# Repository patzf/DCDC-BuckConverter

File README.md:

# DCDC-BuckConverter
HWE Projekt 25/26

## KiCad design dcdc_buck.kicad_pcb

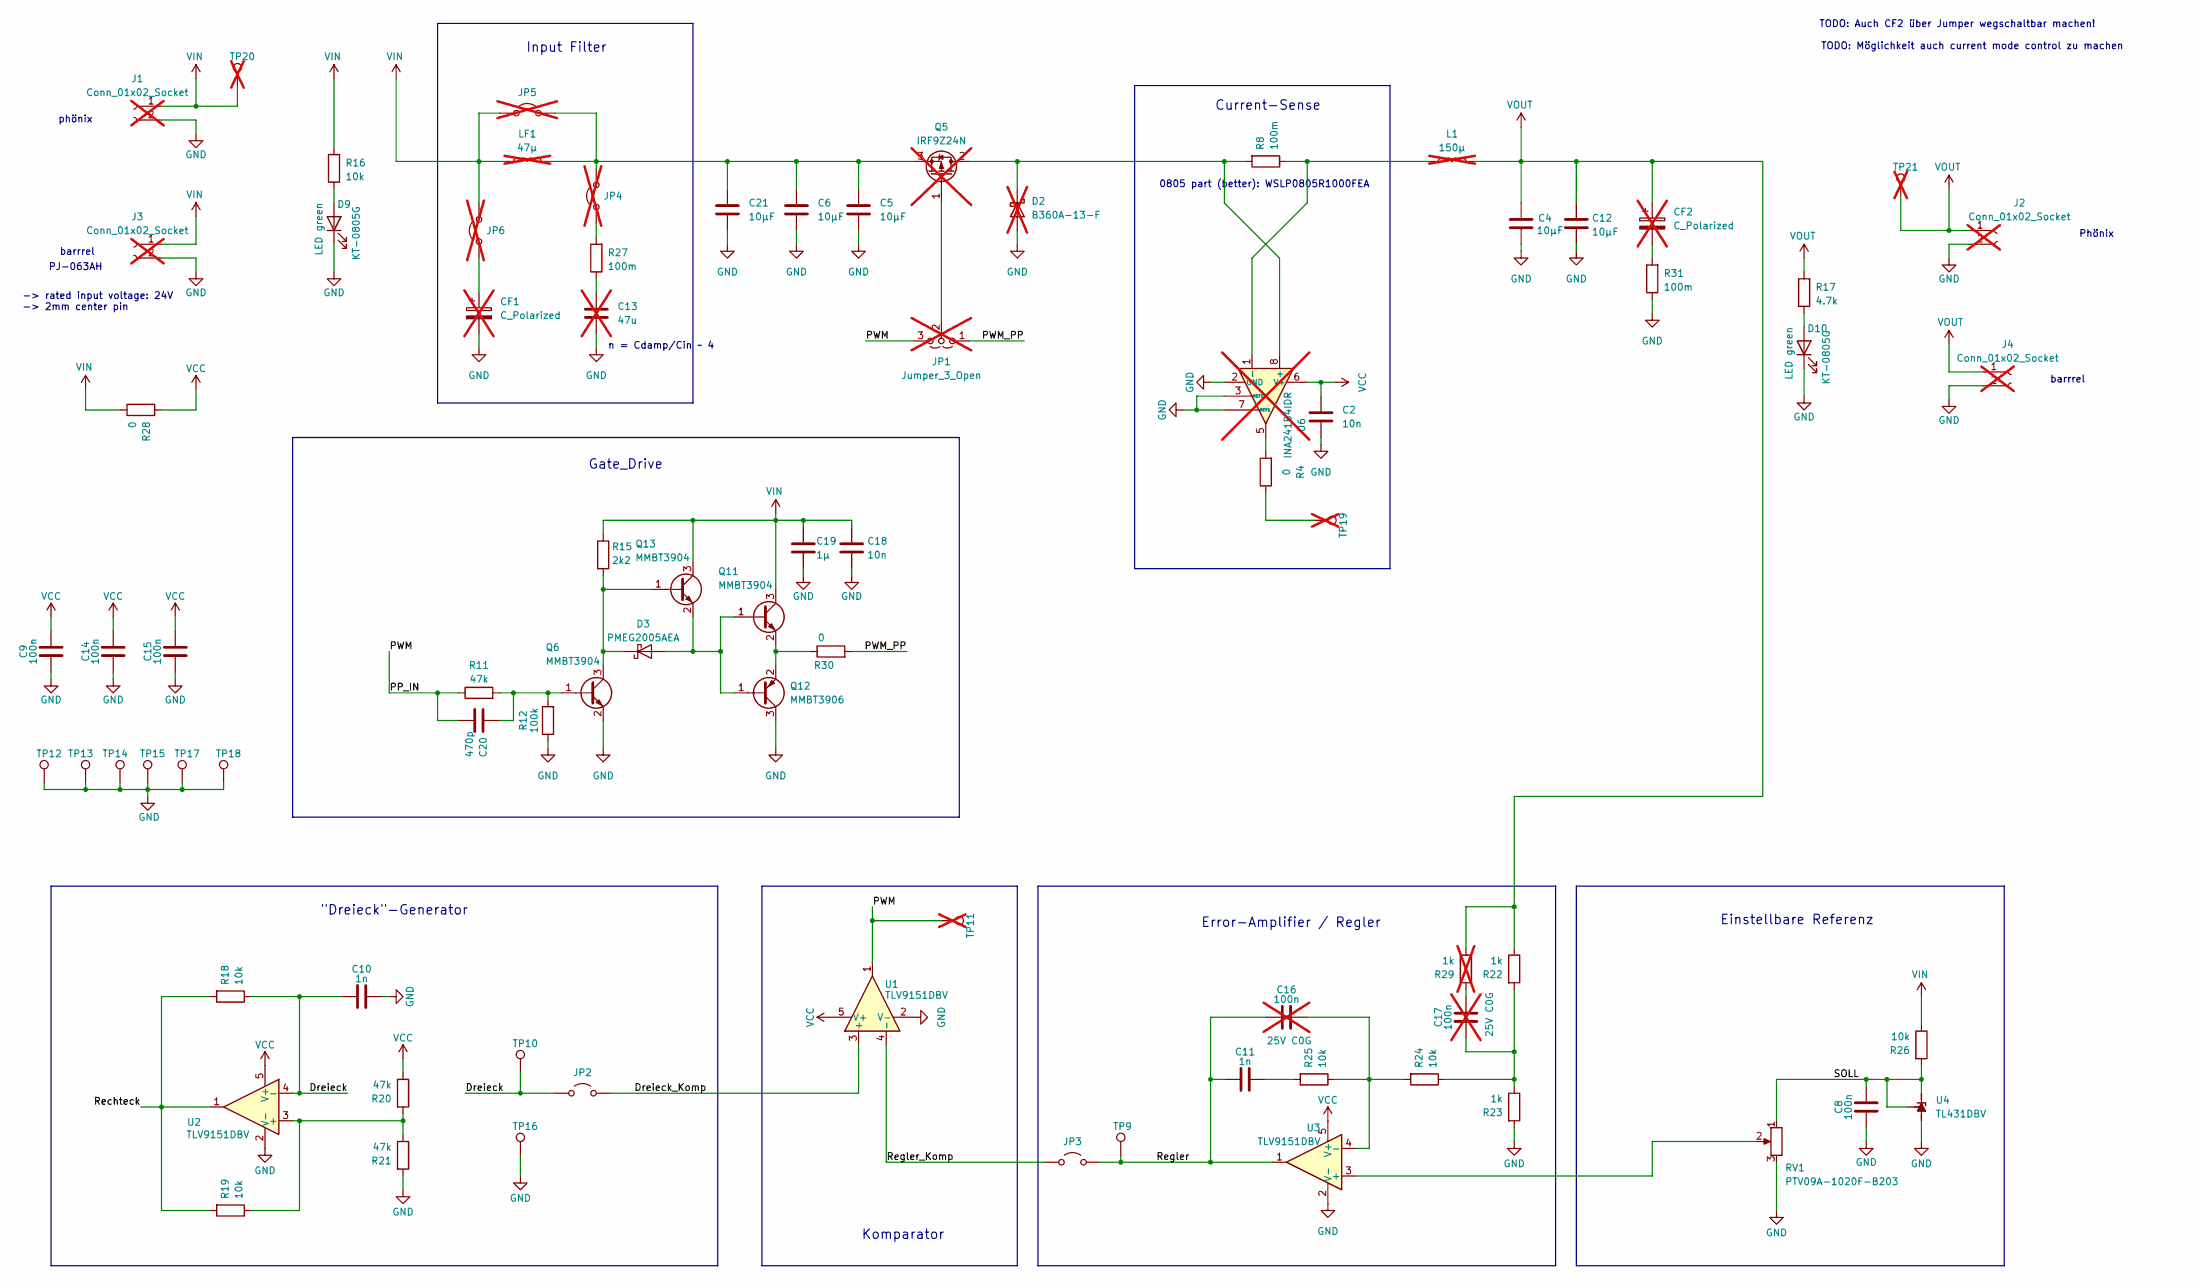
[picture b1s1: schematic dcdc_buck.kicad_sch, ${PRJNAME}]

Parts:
C2, C18: 10n; C_0603_1608Metric_Pad1.08x0.95mm_HandSolder; LCSC Part # C57112
C4, C5, C6, C12, C21: 10µF; C_1206_3216Metric; LCSC Part # C13585
C8: 100n; C_0805_2012Metric; LCSC Part # C49678
C9, C14, C15: 100n; C_0402_1005Metric; LCSC Part # C307331
C10, C11: 1n; C_0805_2012Metric; LCSC Part # C46653
C13: 47u; C_1206_3216Metric; not fitted
C16, C17: 100n; C_0805_2012Metric; not fitted
C19: 1µ; C_0805_2012Metric_Pad1.18x1.45mm_HandSolder; LCSC Part # C28323
C20: 470p; C_0603_1608Metric_Pad1.08x0.95mm_HandSolder; LCSC Part # C1620
CF1, CF2: C_Polarized; CP_Elec_6.3x7.7; not fitted
D2: B360A-13-F; D_SMC; LCSC Part # C94193; not fitted
D3: PMEG2005AEA; D_SOD-323; LCSC Part # C179428
D9, D10: KT-0805G; LED_0805_2012Metric; LCSC Part # C2297
J1, J2: Conn_01x02_Socket; PhoenixContact_MC_1,5_2-G-3.81_1x02_P3.81mm_Horizontal; not fitted
J3, J4: Conn_01x02_Socket; BarrelJack_CUI_PJ-063AH_Horizontal; not fitted
JP1: Jumper_3_Open; PinHeader_1x03_P2.54mm_Vertical; not fitted
JP2, JP3: Jumper_2_Open; PinHeader_1x02_P2.54mm_Vertical; LCSC Part # C492401
JP4, JP5, JP6: Jumper_2_Open; PinHeader_1x02_P2.54mm_Vertical; LCSC Part # C492401; not fitted
L1: 150µ; L_Wurth_WE-PD2-1054; LCSC Part # C6404682; not fitted
LF1: 47µ; L_Wurth_WE-PD2-1054; not fitted
Q5: IRF9Z24N; TO-220-3_Vertical; LCSC Part # C2576; not fitted
Q6, Q11, Q13: MMBT3904; SOT-23; LCSC Part # C20526
Q12: MMBT3906; SOT-23; LCSC Part # C7420354
R4: 0; R_0603_1608Metric_Pad0.98x0.95mm_HandSolder; LCSC Part # C21189
R8, R27, R31: 100m; R_1206_3216Metric_Pad1.30x1.75mm_HandSolder; LCSC Part # C25334
R11: 47k; R_0603_1608Metric_Pad0.98x0.95mm_HandSolder; LCSC Part # C25819
R12: 100k; R_0603_1608Metric_Pad0.98x0.95mm_HandSolder; LCSC Part # C25803
R15: 2k2; R_0805_2012Metric_Pad1.20x1.40mm_HandSolder; LCSC Part # C17520
R16, R18, R19, R24, R25, R26: 10k; R_0805_2012Metric; LCSC Part # C17414
R17: 4.7k; R_0805_2012Metric; LCSC Part # C17673
R20, R21: 47k; R_0805_2012Metric; LCSC Part # C17713
R22, R23: 1k; R_0805_2012Metric; LCSC Part # C17513
R28, R30: 0; R_1206_3216Metric_Pad1.30x1.75mm_HandSolder; LCSC Part # C17888
R29: 1k; R_0805_2012Metric; LCSC Part # C17513; not fitted
RV1: PTV09A-1020F-B203; Potentiometer_Bourns_PTV09A-1_Single_Vertical
TP9, TP10: TestPoint; TP_Keystone_5010-5014_Multipurpose; LCSC Part # C2906765
TP11, TP19, TP20, TP21: TestPoint; TP_Keystone_5010-5014_Multipurpose; LCSC Part # C2906765; not fitted
TP12, TP13, TP14, TP15, TP16, TP17, TP18: TestPoint_Keystone_5019; TestPoint_Keystone_5019_Miniature; LCSC Part # C238131
U1, U2, U3: TLV9151DBV; SOT-23-5; LCSC Part # C1517408
U4: TL431DBV; SOT-23-5
U6: INA241B4IDR; SOIC-8_3.9x4.9mm_P1.27mm; LCSC Part # C21260962; not fitted

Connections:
/Dreieck: C10.2, JP2.1 (A), R18.1, TP10.1 (1_1), U2.4 (-)
/Dreieck_Komp: JP2.2 (B), U1.3 (+)
/PP_IN: C20.2, JP1.3 (B), R11.1, TP11.1 (1_1), U1.1
/PWM_PP: JP1.1 (A), R30.2
/Rechteck: R18.2, R19.2, U2.1
/Regler: C11.2, C16.2, JP3.1 (A), TP9.1 (1_1), U3.1
/Regler_Komp: JP3.2 (B), U1.4 (-)
/SOLL: C8.1, R26.2, RV1.1, U4.3 (K), U4.4 (REF)
GND: C2.2, C4.2, C5.2, C6.2, C8.2, C9.1, C10.1, C12.2, C13.2, C14.1, C15.1, C18.2, C19.2, C21.2, CF1.2, D2.2 (A), D9.1 (K), D10.1 (K), J1.2, J2.2, J3.2, J4.2, Q6.2 (E), Q12.3 (C), R12.1, R21.2, R23.2, R31.1, RV1.3, TP12.1 (1_1), TP13.1 (1_1), TP14.1 (1_1), TP15.1 (1_1), TP16.1 (1_1), TP17.1 (1_1), TP18.1 (1_1), U1.2 (V-), U2.2 (V-), U3.2 (V-), U4.5 (A), U6.2 (GND), U6.3 (REF2), U6.4 (GND), U6.7 (REF1)
unnamed: C11.1, R25.2
unnamed: C13.1, R27.1
unnamed: C17.1, R29.2
unnamed: C17.2, R22.2, R23.1, R24.1
unnamed: CF2.2, R31.2
unnamed: D2.1 (K), Q5.2 (D), R8.2, U6.8 (+)
unnamed: D3.2 (A), Q11.1 (B), Q12.1 (B), Q13.2 (E)
unnamed: D3.1 (K), Q6.3 (C), Q13.1 (B), R15.2
unnamed: D9.2 (A), R16.1
unnamed: D10.2 (A), R17.1
unnamed: JP1.2 (C), Q5.1 (G)
unnamed: C5.1, C6.1, C21.1, JP4.1 (A), JP5.1 (A), LF1.2, Q5.3 (S)
unnamed: JP4.2 (B), R27.2
unnamed: CF1.1, JP6.2 (B)
unnamed: C20.1, Q6.1 (B), R11.2, R12.2
unnamed: Q11.2 (E), Q12.2 (E), R30.1
unnamed: R4.1, TP19.1 (1_1)
unnamed: R4.2, U6.5
unnamed: R19.1, R20.2, R21.1, U2.3 (+)
unnamed: RV1.2, U3.3 (+)
unnamed: C16.1, R24.2, R25.1, U3.4 (-)
unnamed: L1.1, R8.1, U6.1 (-)
VCC: C2.1, C9.2, C14.2, C15.2, R20.1, R28.2, U1.5 (V+), U2.5 (V+), U3.5 (V+), U6.6 (V+)
VIN: C18.1, C19.1, J1.1, J3.1, JP5.2 (B), JP6.1 (A), LF1.1, Q11.3 (C), Q13.3 (C), R15.1, R16.2, R26.1, R28.1, TP20.1 (1_1)
VOUT: C4.1, C12.1, CF2.1, J2.1, J4.1, L1.2, R17.2, R22.1, R29.1, TP21.1 (1_1)

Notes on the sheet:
TODO: Möglichkeit auch current mode control zu machen
-> rated input voltage: 24V -> 2mm center pin
Current-Sense
Komparator
barrrel
"Dreieck"-Generator
Phönix
Einstellbare Referenz
Gate_Drive
n = Cdamp/Cin ~ 4
TODO: Auch CF2 über Jumper wegschaltbar machen!
Error-Amplifier / Regler
0805 part (better): WSLP0805R1000FEA
PJ-063AH
Input Filter
phönix

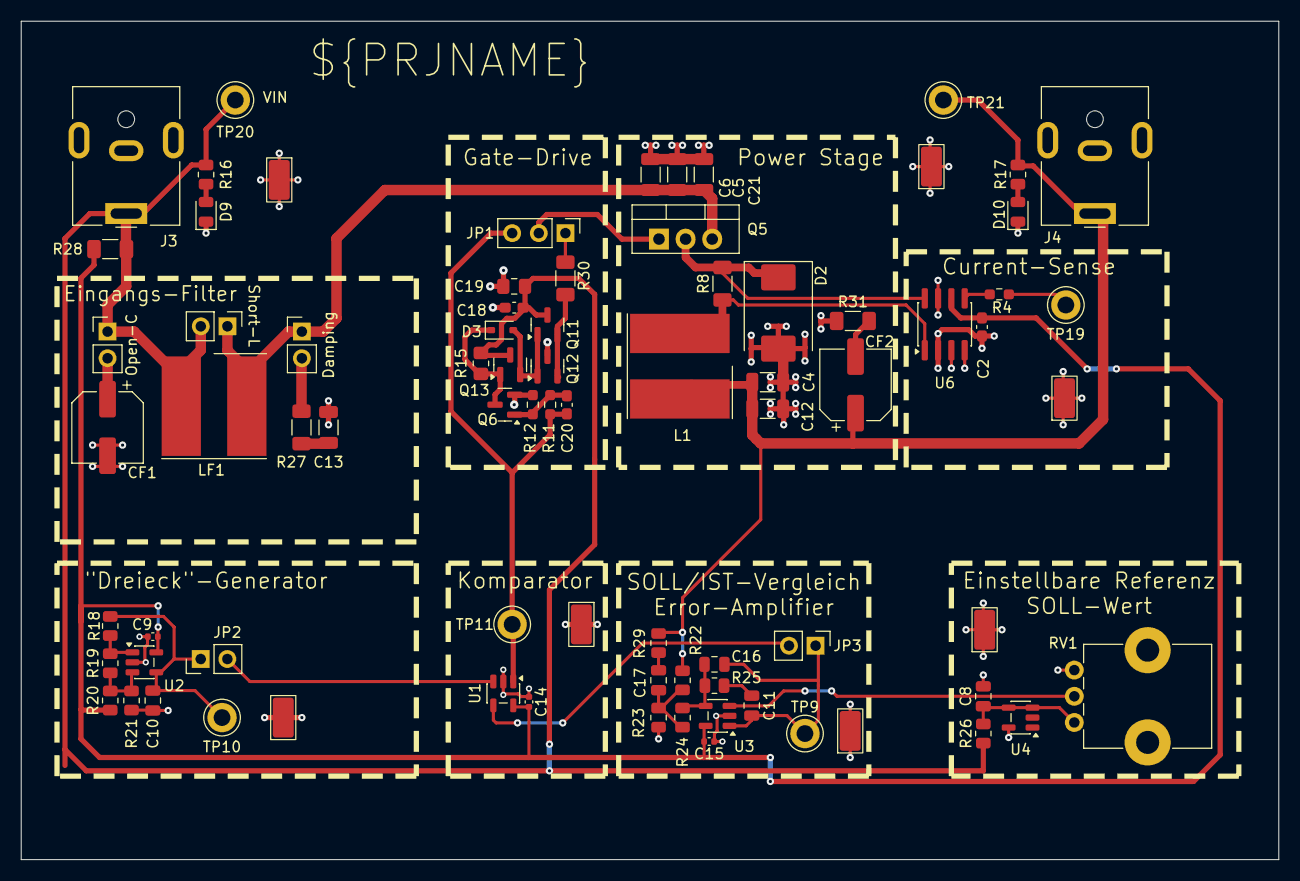
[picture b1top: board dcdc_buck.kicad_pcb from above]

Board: 2 copper layers, 120.0 x 80.0 mm, 79 parts (0 on the bottom side), 34 nets.
